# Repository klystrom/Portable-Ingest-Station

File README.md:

# Portable Ingest Station
**Backup and sync your photos on the go!!!**

## About Portable Ingest Station
This project is intended to solve my worries of backing up my photos while on trips. 

It aims to do the following:

<ol>
  <li>Backup from SD card to local storage (SSD or other targets)</li>
  <li>Backup from local storage to own storage server</li>
</ol>

## Software Requirements
<ol>
  <li>Raspberry Pi OS</li>
  <li>Python</li>
  <li>Git</li>
  <li>KiCAD (for GPIO board)</li>
  <li>NextCloud Server</li>
</ol>

## Hardware Requirements
<ol>
  <li>Raspberry Pi 4 (Only tested on Rpi4 and recommend it for the fast USB file transfer speed and WiFi capability)</li>
  <li>Power supply for Raspberry Pi</li>
  <li>Micro SD card (for Raspberry Pi OS)</li>
  <li>SD Card reader</li>
  <li>Local storage device (In my case it's an SSD in a USB to SATA enclosure)</li>
  <li>RPI GPIO Board</li>
</ol>

# Installation

## YouTube Video:
Overview:
<div align="left">
  
</div>

Software Setup:
<div align="left">
  
</div>

## Step 1: Prepare Raspberry Pi OS
You will need the latest version of [Raspberry Pi OS](https://www.raspberrypi.com/software/). Methods of getting the OS onto the SD card will not be covered here as there are many resources online that covers this. The easiest way is to use the Raspberry Pi Imager.

## Step 2: Boot and Upgrade Raspberry Pi OS
Plug the SD card into Raspberry Pi and power it up. 

> **Note:** If you are doing this process in headless mode (no monitor), you might want to setup wifi connection and SSH access BEFORE plugging in the SD card.

After finished booting up. Complete the usual first boot stuff such as changing default password, expand filesystem, etc.

Update the Raspberry Pi OS by executing the following command:

    sudo apt update && sudo dist-upgrade

Press enter when prompted to proceed with upgrade.

## Step 3: Connection Configuration
When on the go, you probably would not be able to plug the raspberry pi into monitor and keyboard to configure the WiFi connection. So you would need to setup that connection in advance. This internet connection is used by NextCloud to sync the files in your local storage back to your NextCloud server.

Firstly turn on the hotspot on your smartphone. In Raspberry Pi OS, connect to your hotspot SSID. Enter the password. It should have internet access through your smartphone.

> **Note:** If you are doing this process in headless mode, installing VNC would help alot.

## Step 4: Clone Repository
In Raspberry Pi desktop, clone this repository.

    git clone https://github.com/klystrom/Portable-Ingest-Station.git

## Step 5: Setup Nextcloud
This is the part where it gets abit sketchy. Since the the support for official Nextcloud desktop app is non-existent to say the least. So we're going to install an older version of it. It should work after resolving the dependencies.

Guide to install it is [here](https://help.nextcloud.com/t/nextcloud-client-for-raspberry-pi/27989/62). Be sure to follow along the troubleshooting steps mentioned in the thread.

## Step 6: Configure
Plug in your SD card and storage, they should automount under Raspberry Pi OS.

Find out where they are mounted and edit app_nextcloud_sync_check.py.

> **Note:** You can use either of the following commands to find the mountpoints. Look for the keyword "/media/"
>
> df -h
>
> sudo cat /proc/mounts

Your SD card might have different folder structure than mine (mine is based on Fujifilm X-T2 SD Card) and you might want the files to be saved to a specific directory in the local storage. For that, edit the path in these app_nextcloud_sync_check.py.

Now is the most convenient time to test it out. As after this, you would need to reboot the Raspberry Pi in order to test after every change. So put on the GPIO board and test to make sure it works before proceeding to the next step.

## Step 7: Run On Boot
We want the two Python scripts to run on boot. For this, we are using systemd.

> **Note:** Refer [here](https://learn.sparkfun.com/tutorials/how-to-run-a-raspberry-pi-program-on-startup/all) for more info.

Create two new .service files in the systemd directory.

    sudo nano /lib/systemd/system/local_ingest_sync.service
    sudo nano /lib/systemd/system/nextcloud_sync_check.service

Edit local_ingest_sync.service, paste in the following content. Then exit and save by Ctrl+X then enter.

    [Unit]
    Description=Sync SD to local storage
    After=multi-user.target
    
    [Service]
    ExecStart=/usr/bin/python3 <path to repo>/app_portable_ingest_station.py
    
    [Install]
    WantedBy=multi-user.target
    
Edit nextcloud_sync_check.service, paste in the following content. Then exit and save by Ctrl+X then enter.
  
    [Unit]
    Description=Check nextcloud sync status
    After=multi-user.target
    
    [Service]
    ExecStart=/usr/bin/python3 <path to repo>/app_nextcloud_sync_check.py
    
    [Install]
    WantedBy=multi-user.target
    
Enable the services.

    sudo systemctl daemon-reload
    sudo systemctl enable local_ingest_sync.service
    sudo systemctl enable nextcloud_sync_check.service
    
## DONE!
After reboot, everything should be working. Enjoy!

# Limitations
Here are the current limitations that I'm aware of. Feel free to report or help enhance this!
<ol>
  <li>No easy way to connect to another WiFi Network since there's no UI. i.e. hotel WiFi</li>
  <li>Sync status LED not accurate as it depends on the size of a file generated by Nextcloud.</li>
  <li>If the local storage is full, there are no indication.</li>
</ol>

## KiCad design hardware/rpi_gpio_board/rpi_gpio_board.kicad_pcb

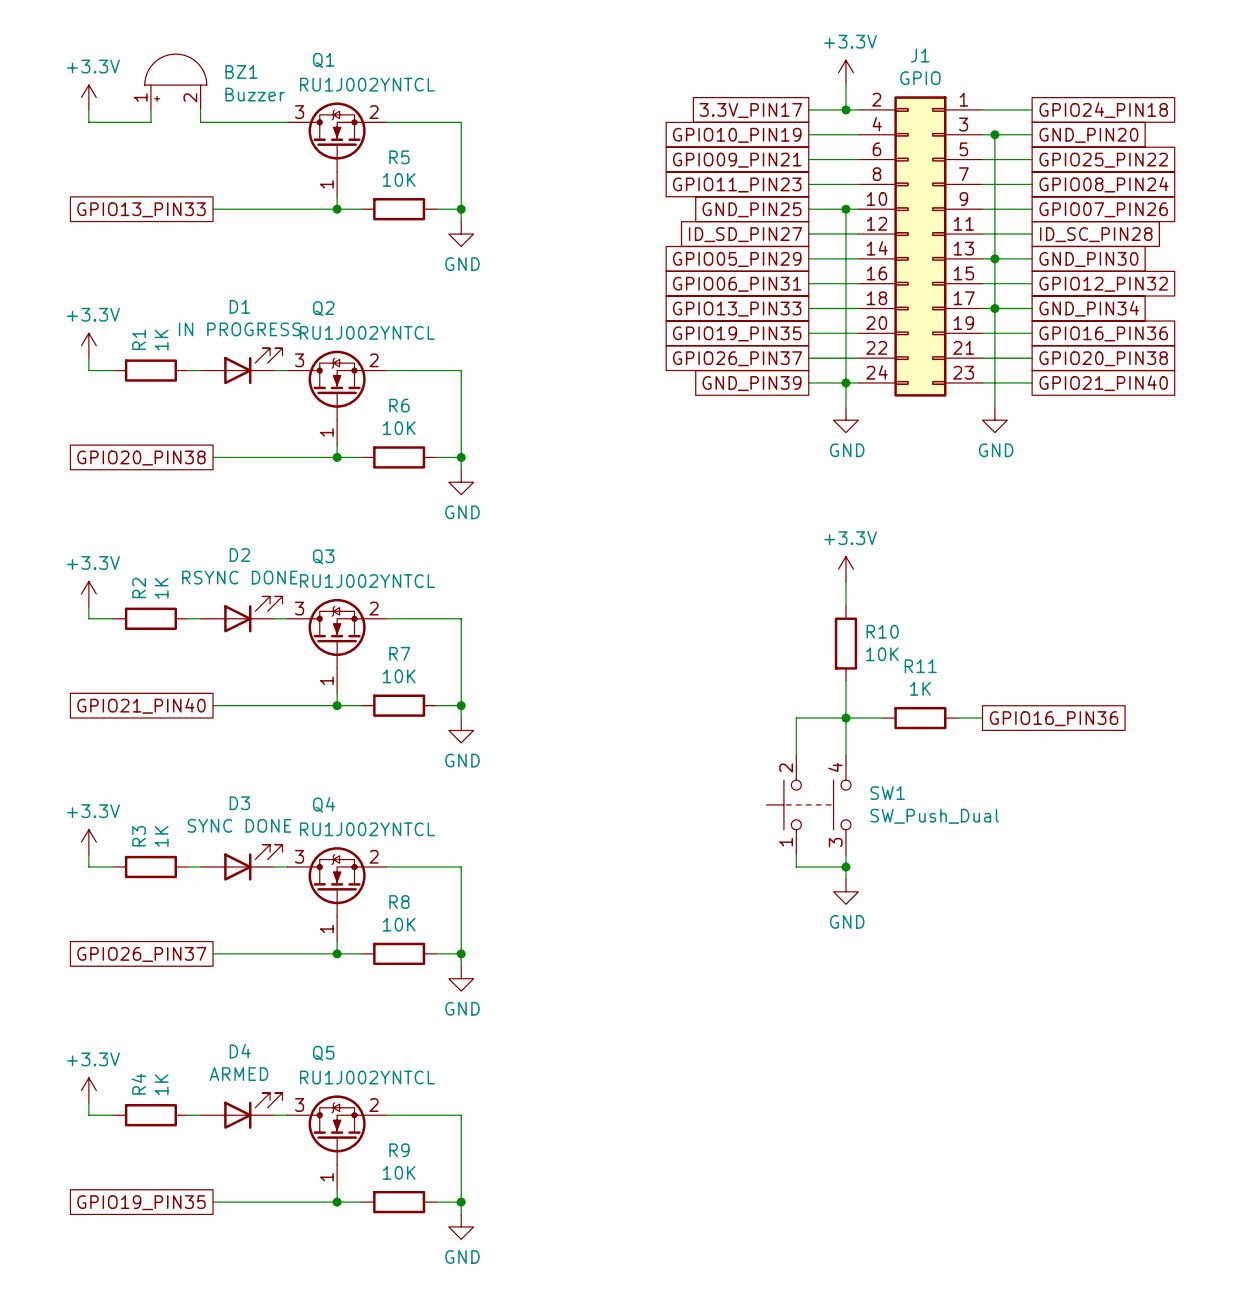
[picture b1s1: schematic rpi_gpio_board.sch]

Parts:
BZ1: Buzzer; Buzzer_12x9.5RM7.6
D1: IN PROGRESS; LED_0603_1608Metric_Pad1.05x0.95mm_HandSolder
D2: RSYNC DONE; LED_0603_1608Metric_Pad1.05x0.95mm_HandSolder
D3: SYNC DONE; LED_0603_1608Metric_Pad1.05x0.95mm_HandSolder
D4: ARMED; LED_0603_1608Metric_Pad1.05x0.95mm_HandSolder
J1: GPIO; PinSocket_2x12_P2.54mm_Vertical
Q1, Q2, Q3, Q4, Q5: RU1J002YNTCL; SOT-323_SC-70_Handsoldering
R1, R2, R3, R4, R11: 1K; R_0603_1608Metric_Pad1.05x0.95mm_HandSolder
R5, R6, R7, R8, R9, R10: 10K; R_0603_1608Metric_Pad1.05x0.95mm_HandSolder
SW1: SW_Push_Dual; TACTILE_SWITCH_SMD_12MM

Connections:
3.3V_PIN17: BZ1.1 (-), J1.2, R1.2, R2.2, R3.2, R4.2, R10.1
GND_PIN20: J1.3, J1.10, J1.13, J1.17, J1.24, Q1.2 (S), Q2.2 (S), Q3.2 (S), Q4.2 (S), Q5.2 (S), R5.1, R6.1, R7.1, R8.1, R9.1, SW1.1, SW1.3
GPIO05_PIN29: J1.14
GPIO06_PIN31: J1.16
GPIO07_PIN26: J1.9
GPIO08_PIN24: J1.7
GPIO09_PIN21: J1.6
GPIO10_PIN19: J1.4
GPIO11_PIN23: J1.8
GPIO12_PIN32: J1.15
GPIO13_PIN33: J1.18, Q1.1 (G), R5.2
GPIO16_PIN36: J1.19, R11.1
GPIO19_PIN35: J1.20, Q5.1 (G), R9.2
GPIO20_PIN38: J1.21, Q2.1 (G), R6.2
GPIO21_PIN40: J1.23, Q3.1 (G), R7.2
GPIO24_PIN18: J1.1
GPIO25_PIN22: J1.5
GPIO26_PIN37: J1.22, Q4.1 (G), R8.2
ID_SC_PIN28: J1.11
ID_SD_PIN27: J1.12
unnamed: BZ1.2 (+), Q1.3 (D)
unnamed: D1.1 (K), Q2.3 (D)
unnamed: D1.2 (A), R1.1
unnamed: D2.1 (K), Q3.3 (D)
unnamed: D2.2 (A), R2.1
unnamed: D3.1 (K), Q4.3 (D)
unnamed: D3.2 (A), R3.1
unnamed: D4.1 (K), Q5.3 (D)
unnamed: D4.2 (A), R4.1
unnamed: R10.2, R11.2, SW1.2, SW1.4

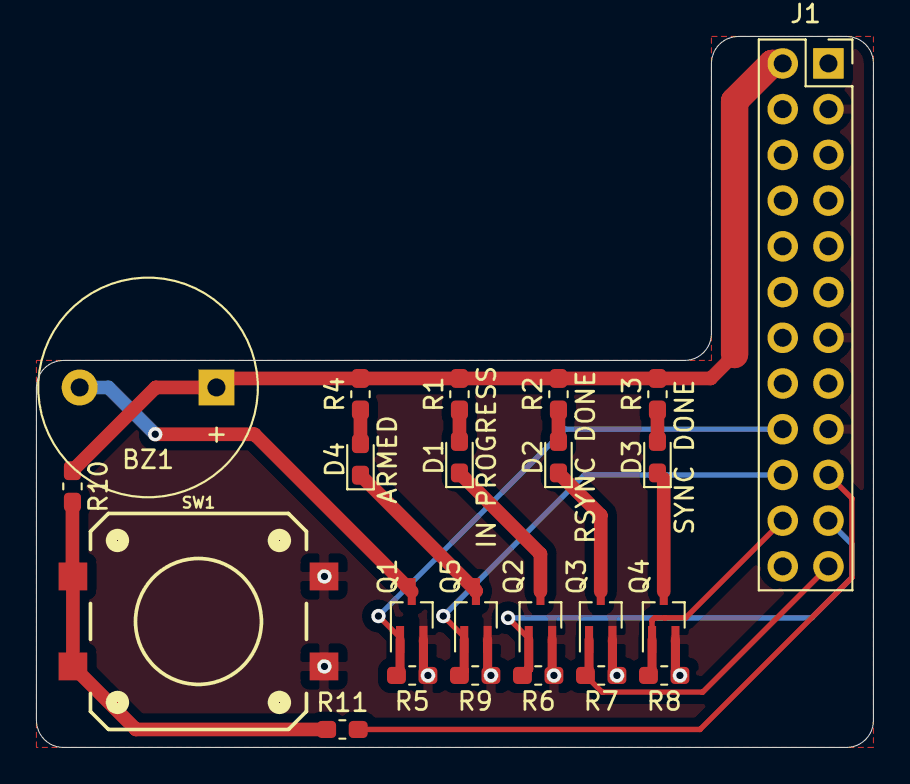
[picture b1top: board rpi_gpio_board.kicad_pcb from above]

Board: 2 copper layers, 46.5 x 39.5 mm, 23 parts (0 on the bottom side), 18 nets.

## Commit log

2021-11-28 First commit.
2021-11-28 added KiCad files
2021-11-28 README
2021-11-28 Markdown syntax correction
2021-11-28 It's Nextcloud, not Owncloud!
2021-11-29 Consolidate the paths to one file
2021-11-29 Additional readme
2021-11-29 Import cleanups
2021-12-14 Added Youtube video link
2021-12-14 update readme for youtube link
2021-12-15 label the youtube video
2021-12-17 overview video
